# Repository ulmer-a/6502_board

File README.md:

# Homebrew 6502 single board computer (running MS BASIC)

This repo contains kicad schematics, netlist, layout and gerber plots for the pcb,
as well as a parts list, the firmware and a port of Microsoft BASIC. The board is
fully functional and all parts (or equivalent alternatives) are readily available
as of Nov '21.

You are welcome to use everything contained in this repository under the
terms of the GNU General Public License v3.0, except for MS BASIC, which is
made available under a BSD 2-clause license.

## Specifications

* 65c02 8-bit CPU along with 32KB RAM and 8K ROM
* 65c22 VIA provides some GPIO pins and timers
* 65c51 ACIA provides a serial port with up to 115200 baud
* 4 status led's (3 of them are freely programmable)
* 18 pin I/O pinheader with general purpose I/O pins (VIA)
* 34 pin expansion pinheader exposing full address and data bus
as well as other interesting lines (`SYNC`, `CLK` and `HALT`)

## Firmware

The firmware initializes the system and provides drivers for the
GPIOs, timers and the UART. It also provides routines to support
the execution of MS BASIC.

## Memory map and I/O addresses

```plaintext
+-----------------------+   <- 0x0000     --.
|       zeropage        |                   |
+-----------------------+   <- 0x0100       |
|        stack          |                   |
+-----------------------+   <- 0x0200       |
|      available        |                   |
|         RAM           |                    > 32k RAM
|         ...           |                   |
+-----------------------+   <- 0x7e00       |
|     UART RX buffer    |                   |
+-----------------------+   <- 0x7f00       |
|     UART TX buffer    |                   |
+-----------------------+   <- 0x8000     --'
|                       |
|      unallocated      |         reserved for expansion shields etc.
|                       |
+-----------------------+   <- 0xdfe0     --.
|      65C51 UART       |                   |
+-----------------------+   <- 0xdff0        > memory mapped I/O
|      65C22 VIA        |                   |
+-----------------------+   <- 0xe000     --:
|     firmware code     |                   |
|    firmware rodata    |                   |
|       MS BASIC        |                    > 8k ROM
+-----------------------+   <- 0xfffa       |
|   reset/irq vectors   |                   |
+-----------------------+   <- 0xffff     --'
```

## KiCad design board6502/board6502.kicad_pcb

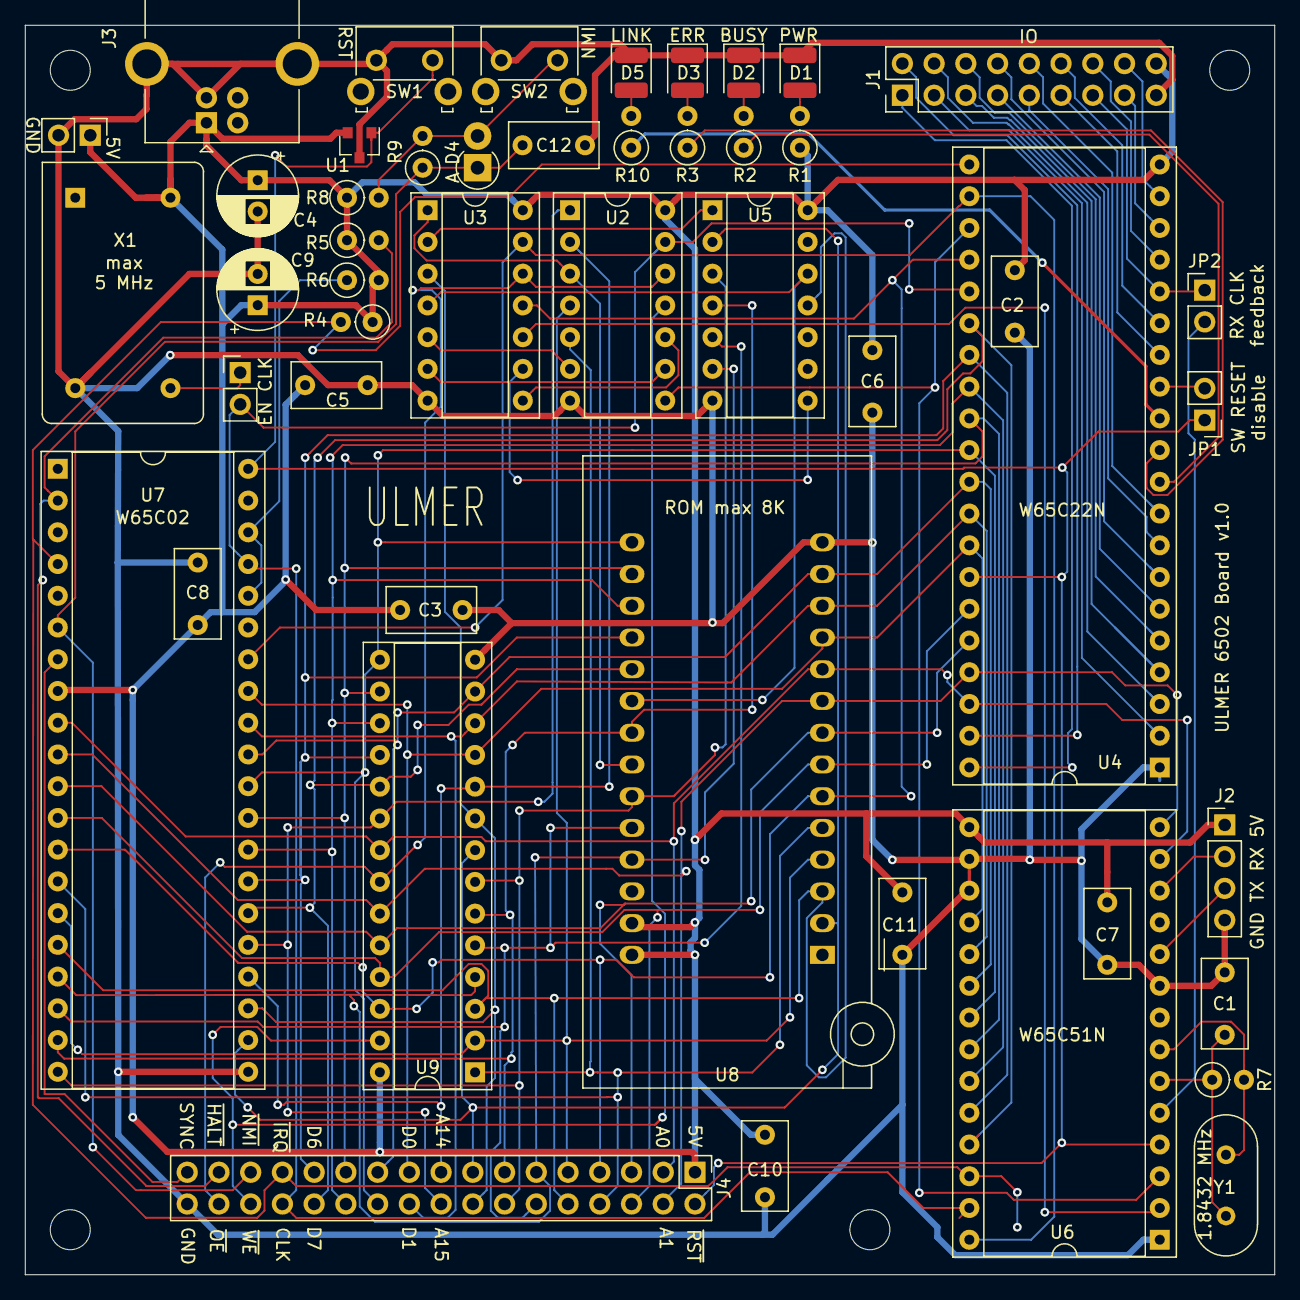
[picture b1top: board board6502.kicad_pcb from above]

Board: 2 copper layers, 100.0 x 100.0 mm, 52 parts (0 on the bottom side), 76 nets.

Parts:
C1: 27p; C_Rect_L7.0mm_W3.5mm_P5.00mm
C2, C3, C5, C6, C7, C8, C10, C11: 100n; C_Rect_L7.0mm_W3.5mm_P5.00mm
C4, C9: 100µ; CP_Radial_D6.3mm_P2.50mm
C12: tbd; C_Rect_L7.0mm_W3.5mm_P5.00mm
D1, D2, D3, D5: LED_Small; LED_1210_3225Metric
D4: tbd; D_DO-41_SOD81_P2.54mm_Vertical_AnodeUp
J1: IO Pinheader; PinHeader_2x09_P2.54mm_Vertical
J2: UART; PinHeader_1x04_P2.54mm_Vertical
J3: USB_B; USB_B_OST_USB-B1HSxx_Horizontal
J4: Expansion Port; PinHeader_2x17_P2.54mm_Vertical
J5: Power connector; PinHeader_1x02_P2.54mm_Vertical
JP1: SW Reset; PinHeader_1x02_P2.54mm_Vertical
JP2: RXCLK feed; PinHeader_1x02_P2.54mm_Vertical
JP3: CLK disable; PinHeader_1x02_P2.54mm_Vertical
M3, M3#2, M3#3, M3#4: MountingHole_3.2mm_M3
R1, R2, R3, R10: 330; R_Axial_DIN0207_L6.3mm_D2.5mm_P2.54mm_Vertical
R4, R5, R6, R8: pullup; R_Axial_DIN0207_L6.3mm_D2.5mm_P2.54mm_Vertical
R7: 1M; R_Axial_DIN0207_L6.3mm_D2.5mm_P2.54mm_Vertical
R9: tbd; R_Axial_DIN0207_L6.3mm_D2.5mm_P2.54mm_Vertical
SW1: Reset button; SW_Tactile_SKHH_Angled
SW2: SW_NMI; SW_Tactile_SKHH_Angled
U1: DS1813; SOT-23
U2: 74LS00; DIP-14_W7.62mm_Socket
U3: 74LS04; DIP-14_W7.62mm_Socket
U4: W65C22N; DIP-40_W15.24mm_Socket
U5: 74LS30; DIP-14_W7.62mm_Socket
U6: W65C51N; DIP-28_W15.24mm_Socket
U7: W65C02; DIP-40_W15.24mm_Socket
U8: AT28C64B; DIP_Socket-28_W11.9_W12.7_W15.24_W17.78_W18.5_3M_228-1277-0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
U9: CY7C199; DIP-28_W7.62mm_Socket
X1: 1-10MHz; Oscillator_DIP-14
Y1: 1.8432M; Crystal_HC18-U_Vertical

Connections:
+5V: C2.1, C3.2, C4.1, C5.1, C6.2, C7.1, C8.2, C9.1, C10.1, C11.2, J1.18, J2.1, J3.1, J4.1, J5.1, R1.1, R4.1, R5.1, R6.2, R8.1, U1.2, U2.14, U3.14, U4.20, U5.14, U6.15, U7.8, U8.27, U8.28, U9.28, X1.14
A0: J4.3, U4.38, U6.13, U7.9, U8.10, U9.21
A1: J4.4, U4.37, U6.14, U7.10, U8.9, U9.23
A2: J4.5, U4.36, U7.11, U8.8, U9.24
A3: J4.6, U4.35, U7.12, U8.7, U9.25
A4: J4.7, U3.11, U4.24, U7.13, U8.6, U9.26
A5: J4.8, U2.5, U7.14, U8.5, U9.1
A6: J4.9, U2.4, U7.15, U8.4, U9.2
A7: J4.10, U5.11, U7.16, U8.3, U9.3
A8: J4.11, U5.6, U7.17, U8.25, U9.4
A9: J4.12, U5.5, U7.18, U8.24, U9.5
A10: J4.13, U5.4, U7.19, U8.21, U9.6
A11: J4.14, U5.3, U7.20, U8.23, U9.7
A12: J4.15, U5.2, U7.22, U8.2, U9.8
A13: J4.16, U3.3, U7.23, U9.9
A14: J4.17, U2.2, U7.24, U9.10
A15: J4.18, U2.1, U7.25, U9.20
CLK: J4.28, JP3.2, U2.13, U4.25, U6.27, U7.37
CS_UART: U3.10, U6.2
D0: J4.19, U4.33, U6.18, U7.33, U8.11, U9.11
D1: J4.20, U4.32, U6.19, U7.32, U8.12, U9.12
D2: J4.21, U4.31, U6.20, U7.31, U8.13, U9.13
D3: J4.22, U4.30, U6.21, U7.30, U8.15, U9.15
D4: J4.23, U4.29, U6.22, U7.29, U8.16, U9.16
D5: J4.24, U4.28, U6.23, U7.28, U8.17, U9.17
D6: J4.25, U4.27, U6.24, U7.27, U8.18, U9.18
D7: J4.26, U4.26, U6.25, U7.26, U8.19, U9.19
GND: C1.2, C2.2, C3.1, C4.2, C5.2, C6.1, C7.2, C8.1, C9.2, C10.2, C11.1, C12.2, D1.1, D2.1, D3.1, D5.1, J1.17, J2.4, J3.4, J3.5, J4.34, J5.2, SW1.1, SW2.1, U1.3, U2.7, U3.7, U4.1, U5.7, U6.1, U6.9, U6.16, U6.17, U7.21, U8.14, U9.14, X1.7
IO1: J1.1, U4.40
IO2: J1.2, U4.39
IO3: J1.3, U4.2
IO4: J1.4, U4.3
IO5: J1.5, U4.4
IO6: J1.6, U4.5
IO7: J1.7, U4.6
IO8: J1.8, U4.7
IO9: J1.9, U4.8
IO10: J1.10, U4.9
IO11: J1.11, U4.14
IO12: J1.12, U4.15
IO13: J1.13, JP2.1, U4.16
IO14: J1.14, U4.17
IO15: J1.15, U4.18
IO16: J1.16, U4.19
LED1: R2.1, U4.10
LED2: R3.1, U4.11
LED3: R10.1, U4.12
unnamed: C1.1, R7.1, U6.6, Y1.1
unnamed: D1.2, R1.2
unnamed: D2.2, R2.2
unnamed: D3.2, R3.2
unnamed: D4.2, R8.2, R9.2, SW2.2
unnamed: D5.2, R10.2
unnamed: JP3.1, X1.8
unnamed: R6.1, U7.36, U7.38
unnamed: R7.2, U6.7, Y1.2
unnamed: U2.6, U3.5
unnamed: U2.9, U3.6
unnamed: U2.10, U3.8
unnamed: U3.2, U5.1
unnamed: U3.9, U5.8
RW_: U3.13, U4.22, U6.28, U7.34
RXCLK: JP2.2, U6.5
SYNC: J4.33, U7.7
UART_RX: J2.2, U6.12
UART_TX: J2.3, U6.10
_CS_ROM: U3.4, U5.12, U8.20
_HALT: J4.31, R5.2, U7.2
_IOSPACE: U2.3, U3.1, U8.22
_IO_CS: U2.8, U4.23, U6.3
_IRQ: J4.27, R4.2, U4.21, U6.26, U7.4
_NMI: C12.1, D4.1, J4.29, R9.1, U7.6
_OE: J4.32, U2.12, U3.12, U9.22
_RESET: J4.2, JP1.1, SW1.2, U1.1, U4.34, U6.4, U7.40
_SW_RESET: JP1.2, U4.13
_WE: J4.30, U2.11, U9.27

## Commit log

2021-09-25 wire up address and data bus of Z80 CPU
2021-09-25 add 8K EEPROM chip to library
2021-09-25 wire up EEPROM
2021-09-25 map EEPROM into address space
2021-09-25 wire up config register
2021-09-25 add W65C51 chip
2021-09-25 update ROM circuit
2021-09-25 add 65C02 chip
2021-09-25 wire up 65c02 cpu
2021-09-25 wire up new CS for the ROM
2021-09-25 wire up static RAM
2021-09-25 add uart chip w65c51
2021-09-25 add address decoding logic
2021-09-25 add 65C22 to library
2021-09-25 wire up VIA
2021-09-25 add caption for VIA
2021-09-26 add reset and power supply circuits
2021-09-26 remove VIA again
2021-09-27 replace barrel jack with micro usb
2021-09-27 rearrange some components
2021-09-27 wire up the 65c22
2021-09-27 complete VIA interface
2021-09-27 make IRQ line wired-or
2021-09-27 new reset circuit
2021-09-27 complete RAM wiring
2021-09-27 rearrange ROM
2021-09-27 rearrange CPU
2021-09-27 wire up UART baud rate generator
2021-09-27 add IO expansion port
2021-09-27 arrange power supply
2021-09-27 address decoding
2021-09-27 fix 6551 crystal
2021-09-27 add RXCLK line to PB6 of VIA
2021-09-27 annotate all parts
2021-09-27 fix small errors
2021-09-27 rename from z80 to 6502
2021-09-27 update IO memory addresses
2021-09-27 update MMIO addresses
2021-09-28 add HALT/SNYC lines to implement hardware debugger
2021-09-28 update gitignore for kicad pcb
2021-09-28 update gitignore
2021-09-28 add README.md
2021-09-28 fix readme
2021-09-28 nicer arrangement of commponents
2021-09-28 create basic firmware version
2021-09-28 add breakpoint handling code
2021-09-29 update to section syntax
2021-09-30 add 1M on UART clk
2021-09-30 update power supply stabilization
2021-09-30 add NMI button
2021-09-30 add values
2021-09-30 start assigning footprints
2021-09-30 preliminary footprint assignment
2021-09-30 add power led
2021-09-30 add vga connector
2021-09-30 add horizontal counter
2021-09-30 generate HSYNC
2021-09-30 save progress on vgaboard
2021-09-30 remove vga board experiments
2021-10-01 add second power port
2021-10-01 annotate, complete up
2021-10-01 add PCB
2021-10-01 start laying out components
2021-10-01 complete layout
2021-10-02 update trace and via sizes
2021-10-02 update net classes
2021-10-02 finally complete PCB routing
2021-10-03 revisit power lines
2021-10-03 redo led traces
2021-10-03 satisfy design rules
2021-10-03 move silkscreen out of the way
2021-10-03 add mounting holes
2021-10-03 fix design rule violation
2021-10-03 add component annotation
2021-10-03 annotate expansion bus
2021-10-07 plot gerber files
2021-10-07 add LICENSE
2021-10-30 add hello world firmware
2021-10-31 update firmware: read UART in IRQ mode
2021-11-30 rewrite firmware for rust assembler
2021-11-30 fix getchar()
2021-12-02 setup makefile for firmware build
2021-12-02 progress on uart driver
2021-12-02 reformat uart driver code
2021-12-02 make board boot with the current firmware
2021-12-02 make UART receive work
2021-12-02 reformat uart code
2021-12-02 add echo_on(), echo_off()
2021-12-02 make RX ringbuffer work
2021-12-02 handle overflow in RX ringbuffer
2021-12-02 add documentation comments to the uart driver
2021-12-02 remove duplicate code
2021-12-03 bump up baud rate to 115200
2021-12-03 add seperate source file for i/o driver
2021-12-03 setup via interrupt handling
2021-12-03 implement buffer-fed timer-driven uart transmit
2021-12-03 fine-tune timer value for uart transmit timer
2021-12-03 put vectors into their own file
2021-12-03 split up parts of uart.S into stdio.S
2021-12-04 replace rendering with actual assembled board
2022-05-29 update makefile
2022-06-06 implement program loader (not tested)
2022-06-06 can build MS BASIC
2022-06-06 fixing rom layout and make gw basic run
2022-06-06 add copyright notice for msbasic
2022-06-06 generate debug info
2022-06-07 make BASIC branding customizable
